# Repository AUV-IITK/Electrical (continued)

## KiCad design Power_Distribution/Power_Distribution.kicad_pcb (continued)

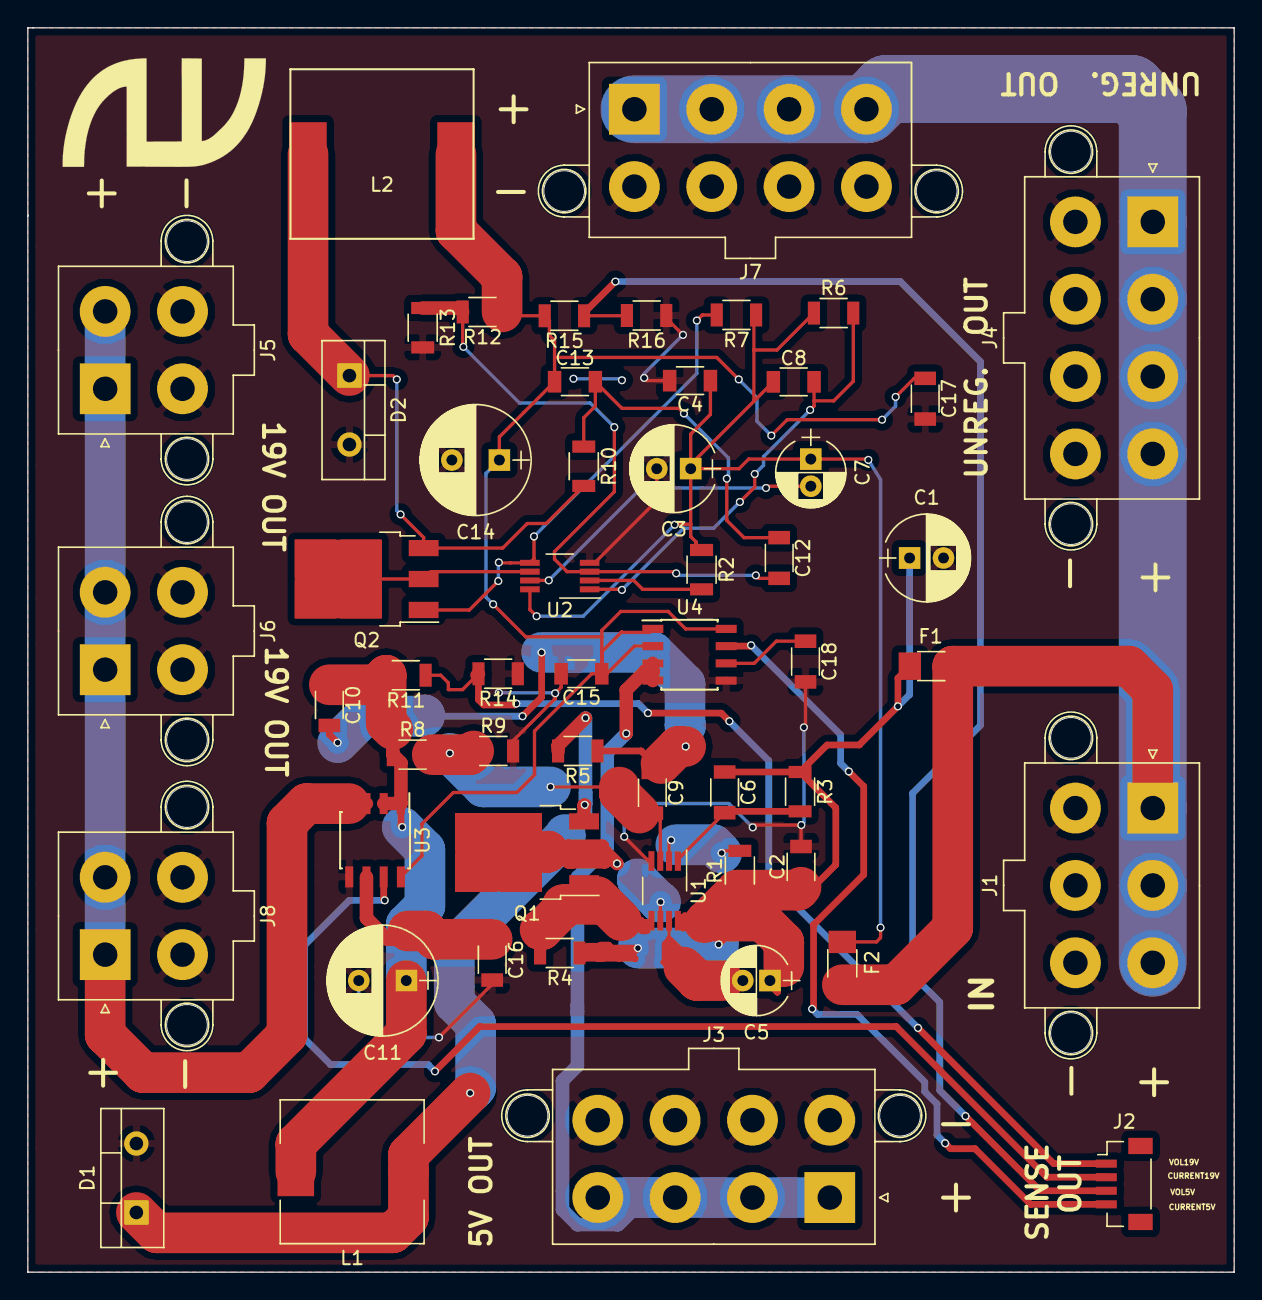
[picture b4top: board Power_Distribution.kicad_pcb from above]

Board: 2 copper layers, 88.9 x 91.7 mm, 54 parts (0 on the bottom side), 30 nets.

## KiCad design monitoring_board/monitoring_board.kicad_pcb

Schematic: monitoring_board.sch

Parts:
D3, D4, D5, D6, D7, D8, D9: LED; LED_D5.0mm
DS1: WC1602A
F1: 30A Polyfuse; Fuse_TE5_Littlefuse-395Series
F2: 4A Polyfuse; Fuse_TE5_Littlefuse-395Series
J1, J2, J3, J4, J7, J8, J9, J10, J11, J12, J13: Conn_01x02; TerminalBlock_bornier-2_P5.08mm
J5: Conn_01x05; Pin_Header_Straight_1x05_Pitch2.54mm
J6: Conn_02x08_Odd_Even; Pin_Header_Straight_2x08_Pitch2.54mm
P1, P17: Digital; Socket_Strip_Arduino_2x18
P2, P14: Power; Socket_Strip_Arduino_1x08
P3, P4, P15, P16: Analog; Socket_Strip_Arduino_1x08
P5, P18: PWM; Socket_Strip_Arduino_1x10
P6, P19: PWM; Socket_Strip_Arduino_1x08
P7, P20: Communication; Socket_Strip_Arduino_1x08
P8, P9, P10, P11, P12, P13, P21, P22, P23, P24, P25, P26: CONN_01X01; Arduino_1pin
Q1, Q2: Q_PMOS_GDS; TO-252-2
R1, R2, R13, R15, R17, R19, R21, R23, R25, R27, R29, R31, R33, R34, R35, R36, R37, R38, R39, R40, R43, R44: 1K; R_Axial_DIN0207_L6.3mm_D2.5mm_P10.16mm_Horizontal
R3, R4, R5, R6, R7, R8, R9, R10, R11: 50m; R_Axial_DIN0207_L6.3mm_D2.5mm_P10.16mm_Horizontal
R12, R14, R16, R18, R20, R22, R24, R26, R28, R30, R32: 24K; R_Axial_DIN0207_L6.3mm_D2.5mm_P10.16mm_Horizontal
R41: R; R_Axial_DIN0207_L6.3mm_D2.5mm_P10.16mm_Horizontal
R42: 220; R_Axial_DIN0207_L6.3mm_D2.5mm_P10.16mm_Horizontal
SW1, SW2: SW_DIP_x01; TerminalBlock_bornier-2_P5.08mm

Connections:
+3V3: J5.2, P2.4, P14.4
+5V: DS1.2, J5.1, P1.35, P1.36, P2.5, P14.5, P17.35, P17.36, R37.2, R42.1
/0(Rx0): P6.8, P19.8
/1(Tx0): P6.7, P19.7
/2(**): J6.1, P6.6, P19.6
/3(**): J6.3, P6.5, P19.5
/4(**): J6.5, P6.4, P19.4
/5(**): J6.7, P6.3, P19.3
/6(**): J6.9, P6.2, P19.2
/7(**): J6.11, P6.1, P19.1
/8(**): J6.13, P5.10, P18.10
/9(**): J6.15, P5.9, P18.9
/10(**): P5.8, P18.8
/11(**): P5.7, P18.7
/12(**): P5.6, P18.6
/13(**): P5.5, P18.5, R36.2
/14(Tx3): P7.1, P20.1
/15(Rx3): P7.2, P20.2
/16(Tx2): P7.3, P20.3
/17(Rx2): P7.4, P20.4
/18(Tx1): P7.5, P20.5
/19(Rx1): P7.6, P20.6
/20(SDA): J5.3, P7.7, P20.7, R38.2
/21(SCL): J5.4, P7.8, P20.8, R39.2
/22: P1.33, P17.33, R40.2
/23: DS1.11, P1.34, P17.34
/24: DS1.12, P1.31, P17.31
/25: DS1.13, P1.32, P17.32
/26: DS1.14, P1.29, P17.29
/27: DS1.6, P1.30, P17.30
/28: DS1.4, P1.27, P17.27
/29: P1.28, P17.28
/30: P1.25, P17.25
/31: P1.26, P17.26
/32: P1.23, P17.23
/33: P1.24, P17.24
/34: P1.21, P17.21
/35: P1.22, P17.22
/36: P1.19, P17.19
/37: P1.20, P17.20
/38: P1.17, P17.17
/39: P1.18, P17.18
/40: P1.15, P17.15
/41: P1.16, P17.16
/42: P1.13, P17.13
/43: P1.14, P17.14
/44: P1.11, P17.11
/45: P1.12, P17.12
/46: P1.9, P17.9
/47: P1.10, P17.10
/48: P1.7, P17.7
/49: P1.8, P17.8
/50(MISO): P1.5, P17.5
/51(MOSI): P1.6, P17.6
/52(SCK): P1.3, P17.3
/53(SS): P1.4, P17.4
/A0: P3.1, P15.1, R16.1, R17.2
/A1: P3.2, P15.2, R12.1, R13.2
/A2: P3.3, P15.3, R20.1, R21.2
/A3: P3.4, P15.4, R24.1, R25.2
/A4: P3.5, P15.5, R32.1, R33.2
/A5: P3.6, P15.6, R14.1, R15.2
/A6: P3.7, P15.7, R18.1, R19.2
/A7: P3.8, P15.8, R26.1, R27.2
/A8: P4.1, P16.1, R30.1, R31.2
/A9: P4.2, P16.2, R22.1, R23.2
/A10: P4.3, P16.3, R28.1, R29.2
/A11: P4.4, P16.4
/A12: P4.5, P16.5
/A13: P4.6, P16.6
/A14: P4.7, P16.7
/A15: P4.8, P16.8
/AREF: P5.3, P18.3
/IOREF: P2.2, P14.2
/Reset: P2.3, P14.3
/SCL: P5.1, P18.1
/SDA: P5.2, P18.2
/VBATT1: Q1.2, SW1.2
/VBATT2: Q2.2, SW2.2
/VESC1: J3.1, R4.1, R12.2
/VESC2: J7.1, R5.1, R20.2
/VESC3: J8.1, R6.1, R24.2
/VESC4: J9.1, R7.1, R32.2
/VESC5: J10.1, R8.1, R14.2
/VESC6: J11.1, R9.1, R18.2
/VESC7: J12.1, R10.1, R26.2
/VESC8: J13.1, R11.1, R30.2
/VIN1: F1.1, R4.2, R5.2, R6.2, R7.2, R8.2, R9.2, R10.2, R11.2, R16.2, R34.2
/VIN2: F2.1, R3.2, R22.2, R35.2
/VNUC: J4.1, R3.1, R28.2
/Vin: P2.8, P14.8
GND: D3.1, D4.1, D5.1, D6.1, D7.1, D8.1, D9.1, DS1.1, DS1.5, DS1.16, J1.2, J2.2, J3.2, J4.2, J5.5, J6.2, J6.4, J6.6, J6.8, J6.10, J6.12, J6.14, J6.16, J7.2, J8.2, J9.2, J10.2, J11.2, J12.2, J13.2, P1.1, P1.2, P2.6, P2.7, P5.4, P14.6, P14.7, P17.1, P17.2, P18.4, R1.1, R2.1, R13.1, R15.1, R17.1, R19.1, R21.1, R23.1, R25.1, R27.1, R29.1, R31.1, R33.1, R41.1
unnamed: D3.2, R34.1
unnamed: D4.2, R35.1
unnamed: D5.2, R36.1
unnamed: D6.2, R37.1
unnamed: D7.2, R38.1
unnamed: D8.2, R39.1
unnamed: D9.2, R40.1
unnamed: DS1.3, R41.2
unnamed: DS1.15, R42.2
unnamed: F1.2, Q1.3, R43.2
unnamed: F2.2, Q2.3, R44.2
unnamed: J1.1, SW1.1
unnamed: J2.1, SW2.1
unnamed: Q1.1, R1.2, R43.1
unnamed: Q2.1, R2.2, R44.1

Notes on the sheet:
Shield for Arduino Mega Rev 3
Holes
Pin duplicates for future use/debugging

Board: 2 copper layers, 97 parts (0 on the bottom side), 107 nets, no tracks yet.

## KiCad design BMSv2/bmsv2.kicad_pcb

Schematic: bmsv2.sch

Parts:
C1, C7: 10n; C_1206
C2, C8, C25, C26, C27, C28, C41, C42, C43, C44, C45, C48, C51: 0.1u; C_1206
C3: 3300p; C_1206
C4, C6, C10, C12: 50u; C_1206
C5: 33p; C_1206
C9: 735p; C_1206
C11: 7.35p; C_1206
C13, C15, C16, C39: 10u; C_1206
C14, C17, C18, C19, C20, C21, C22, C23, C24, C30, C31, C32, C33, C34, C35, C36, C37, C38: 1u; C_1206
C46, C47, C49, C50, C52, C53: 1n; C_1206
CS1, CS2, CS3: ACS725LLC; SOIC-8_3.9x4.9mm_Pitch1.27mm
D1, D3, D4, D5, D6: LED; D_1206
D2: 3.6V; D_1206
D7: 19V; D_1206
D8, D10: D; D_1206
D9, D11: D_Zener; D_1206
F1, F2: Fuse; Fuse_SMD1206_Reflow
J1: B1; Molex_MegaFit_2x01x5.70mm_Angled
J2: B0; Molex_MegaFit_2x01x5.70mm_Angled
J3: BC1; Wafer_Horizontal20x5.8x7RM2.5-7
J4: BC0; Wafer_Horizontal20x5.8x7RM2.5-7
J5: UnRegA; Molex_MegaFit_2x01x5.70mm_Angled
J6: UnRegB; Molex_MegaFit_2x01x5.70mm_Angled
J7: 15V0A; Molex_MegaFit_2x01x5.70mm_Angled
J8: 15V0B; Molex_MegaFit_2x01x5.70mm_Angled
J9: 3V3A; Molex_MegaFit_2x01x5.70mm_Angled
J10: 3V3B; Molex_MegaFit_2x01x5.70mm_Angled
J11: TFT_Header; Berg_11x01
J12: USB_B
J13: Atxmega_Header; Berg_10x02
L1, L2: 20u; L_1206
Q1, Q2, Q5, Q8: Q_PMOS_GSD; SOT-23
Q3, Q4, Q6, Q7: Q_NMOS_GSD; SOT-23
R1, R11: 330K; R_1206
R2, R12: 21K; R_1206
R3, R5, R13, R34, R35, R36, R37, R38, R39, R40, R41, R55, R56, R57, R58, R59, R60, R61, R62: 1K; R_1206
R4: 150; R_1206
R6: 250K; R_1206
R7, R17: 80K; R_1206
R8: 25K; R_1206
R9, R19, R22, R27, R28, R42, R51, R52, R72, R73, R78: 10K; R_1206
R10: 500; R_1206
R14, R15: 2K; R_1206
R16: 1420K; R_1206
R18: 112K; R_1206
R20, R21, R45, R49, R50, R76: 100K; R_1206
R23, R25, R26, R31, R32, R43, R44, R53, R63, R64, R67, R68, R74, R75: 100R; R_1206
R24, R71: 350K; R_1206
R29, R30, R33, R47, R48, R54, R65, R66, R69, R70: 1M; R_1206
R46, R77: R; R_1206
U1, U2: TPS54531; SOIC-8-1EP_3.9x4.9mm_Pitch1.27mm
U3: ATXMEGA128A1U-AU; TQFP-100_14x14mm_Pitch0.5mm
U4, U6: BQ76930; SSOP-20_4.4x6.5mm_Pitch0.65mm
U5, U7: BQ78350-R1; TSSOP-30_4.4x7.8mm_Pitch0.5mm

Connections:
+BATT: CS1.1, CS1.2, F1.1, F2.1, R1.1, R11.1, R23.2, R24.2, R53.2, R71.2, U1.2, U2.2, U4.9, U6.9
/3.3V_CS: CS3.3, CS3.4, J9.1, J10.1
/15V_CS: CS2.3, CS2.4, J7.1, J8.1
/A0: J13.4, U3.6
/A1: J13.6, U3.9
/A2: J13.8, U3.10
/ALERT0: U4.30, U5.2
/ALERT1: U6.30, U7.2
/AREF: J13.2, U3.5
/B0P0: J2.1, Q1.3
/B1P0: J1.1, Q2.3
/BAT0: R24.1, R42.2, U5.7
/BAT1: R71.1, R78.2, U7.7
/BATT_CS: CS1.3, CS1.4, J5.1, J6.1
/C01: J4.6, R35.1
/C02: J4.5, R36.1
/C03: J4.4, R37.1
/C04: J4.3, R38.1
/C05: J4.2, R39.1, R40.1
/C06: J4.1, R41.1
/C11: J3.6, R56.1
/C12: J3.5, R57.1
/C13: J3.4, R58.1
/C14: J3.3, R59.1
/C15: J3.2, R60.1, R61.1
/C16: J3.1, R62.1
/CHG0: Q5.2, U4.2
/CHG1: Q8.2, U6.2
/CSO0: C46.1, CS1.7
/CSO1: C49.1, CS2.7
/CSO2: C52.1, CS3.7
/D0: J13.10, U3.27
/D1: J13.12, U3.28
/D2: J13.14, U3.29
/D3: J13.16, U3.30
/D4: J13.18, U3.17
/D5: J13.20, U3.18
/DAC0: J13.17, U3.97
/DAC1: J13.19, U3.98
/DSG0: Q3.1, R33.1, U4.1
/DSG1: Q6.1, R54.1, U6.1
/MISO: J13.5, U3.21
/MOSI: J13.3, U3.20
/REGOUT0: R20.2, R21.2, R27.1, R28.1, R45.1, U4.8, U5.26
/REGOUT1: R49.2, R50.2, R72.1, R73.1, R76.1, U6.8, U7.26
/RSNS0: Q3.2, R33.2, R43.1, R46.2
/RSNS1: Q6.2, R54.2, R74.1, R77.2
/RX: J13.9, U3.37
/SCK: J13.7, U3.22
/SCL: J13.15, U3.36
/SCL0: R27.2, U4.5, U5.4
/SCL1: R72.2, U6.5, U7.4
/SDA: J13.13, U3.35
/SDA0: R28.2, U4.4, U5.3
/SDA1: R73.2, U6.4, U7.3
/SMBC0: R26.2, U5.13
/SMBC1: R64.2, U7.13
/SMBD0: R25.2, U5.11
/SMBD1: R63.2, U7.11
/SS: J13.1, U3.19
/TFT_CS: J11.7, U3.50
/TFT_DC: J11.9, U3.52
/TFT_MOSI: J11.6, U3.40
/TFT_RESET: J11.8, U3.51
/TFT_SCK: J11.4, U3.42
/TX: J13.11, U3.38
/USBD+: J12.3, U3.32
/USBD-: J12.2, U3.31
/USB_VCC: R3.1, R5.2, U3.99
/VC00: C17.2, R34.2, U4.27
/VC01: C18.2, C19.1, R35.2, U4.26
/VC02: C19.2, C20.1, R36.2, U4.25
/VC03: C20.2, C21.1, R37.2, U4.24
/VC04: C21.2, C22.1, R38.2, U4.23
/VC05: C22.2, C23.1, C24.1, R39.2, U4.22
/VC05B: C23.2, R40.2, U4.21
/VC06: C24.2, R41.2, U4.20
/VC10: C31.2, R55.2, U6.27
/VC11: C32.2, C33.1, R56.2, U6.26
/VC12: C33.2, C34.1, R57.2, U6.25
/VC13: C34.2, C35.1, R58.2, U6.24
/VC14: C35.2, C36.1, R59.2, U6.23
/VC15: C36.2, C37.1, C38.1, R60.2, U6.22
/VC15B: C37.2, R61.2, U6.21
/VC16: C38.2, R62.2, U6.20
/uSCL0: R32.1, U3.16
/uSCL1: R68.1, U3.26
/uSDA0: R31.1, U3.15
/uSDA1: R67.1, U3.25
GND: C1.2, C4.2, C5.1, C6.2, C7.2, C10.2, C11.1, C12.2, C13.1, C14.2, C15.1, C16.2, C17.1, C18.1, C26.1, C27.1, C28.1, C30.2, C31.1, C32.1, C39.2, C42.1, C43.1, C44.1, C45.2, C46.2, C47.2, C48.2, C49.2, C50.2, C51.2, C52.2, C53.2, CS1.5, CS2.5, CS3.5, D1.1, D2.2, D3.1, D4.1, D5.1, D6.1, D7.2, D9.2, D11.2, J1.2, J2.2, J3.7, J4.7, J5.2, J6.2, J7.2, J8.2, J9.2, J10.2, J11.3, J12.4, J12.5, Q1.1, Q2.1, Q4.2, Q5.1, Q7.2, Q8.1, R2.2, R5.1, R7.2, R8.1, R12.2, R17.2, R18.1, R19.2, R29.2, R30.2, R34.1, R42.1, R44.1, R46.1, R47.2, R51.2, R55.1, R65.2, R66.2, R69.2, R75.1, R77.1, R78.1, U1.7, U2.7, U3.3, U3.13, U3.23, U3.33, U3.43, U3.53, U3.63, U3.73, U3.84, U3.93, U4.3, U5.8, U5.9, U5.22, U5.23, U5.25, U5.30, U6.3, U7.8, U7.9, U7.22, U7.23, U7.25, U7.30
unnamed: C1.1, U1.4
unnamed: C2.1, D2.1, L1.1, U1.8
unnamed: C2.2, U1.1
unnamed: C3.1, R8.2
unnamed: C3.2, C5.2, U1.6
unnamed: C7.1, U2.4
unnamed: C8.1, D7.1, L2.1, U2.8
unnamed: C8.2, U2.1
unnamed: C9.1, R18.2
unnamed: C9.2, C11.2, U2.6
unnamed: C14.1, U4.7
unnamed: C16.1, R23.1, U4.15
unnamed: C25.1, C27.2, R43.2, U4.29
unnamed: C25.2, C28.2, R44.2, U4.28
unnamed: C26.2, U5.27
unnamed: C30.1, U6.7
unnamed: C39.1, R53.1, U6.15
unnamed: C41.1, C43.2, R74.2, U6.29
unnamed: C41.2, C44.2, R75.2, U6.28
unnamed: C42.2, U7.27
unnamed: C45.1, CS1.8
unnamed: C47.1, CS1.6
unnamed: C48.1, CS2.8
unnamed: C50.1, CS2.6
unnamed: C51.1, CS3.8
unnamed: C53.1, CS3.6
unnamed: D1.2, R4.2
unnamed: D3.2, R10.2
unnamed: D4.2, R13.2
unnamed: D5.2, R14.1
unnamed: D6.2, R15.1
unnamed: D8.1, D9.1, Q4.1, R47.1, R48.2
unnamed: D8.2, Q5.3, R48.1
unnamed: D10.1, D11.1, Q7.1, R69.1, R70.2
unnamed: D10.2, Q8.3, R70.1
unnamed: F1.2, Q1.2, R14.2
unnamed: F2.2, Q2.2, R15.2
unnamed: J12.1, R3.2
unnamed: Q3.3, Q4.3
unnamed: Q6.3, Q7.3
unnamed: R1.2, R2.1, U1.3
unnamed: R6.2, R7.1, U1.5
unnamed: R9.1, U3.90
unnamed: R10.1, U3.49
unnamed: R11.2, R12.1, U2.3
unnamed: R16.2, R17.1, U2.5
unnamed: R19.1, U4.6
unnamed: R20.1, U5.12
unnamed: R21.1, U5.14
unnamed: R22.1, U4.10
unnamed: R22.2, U4.13
unnamed: R25.1, R29.1, R31.2
unnamed: R26.1, R30.1, R32.2
unnamed: R45.2, U5.24
unnamed: R49.1, U7.12
unnamed: R50.1, U7.14
unnamed: R51.1, U6.6
unnamed: R52.1, U6.10
unnamed: R52.2, U6.13
unnamed: R63.1, R65.1, R67.2
unnamed: R64.1, R66.1, R68.2
unnamed: R76.2, U7.24
unnamed: U4.11, U4.12, U4.14
unnamed: U6.11, U6.12, U6.14

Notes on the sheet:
Connectors
RP, OC Protection
Atxmega
Buck Converters
BM ICs
BM FETs
BM Cell Side
Copyright. AUV-IITK www.auviitk.com
Current Sensors

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
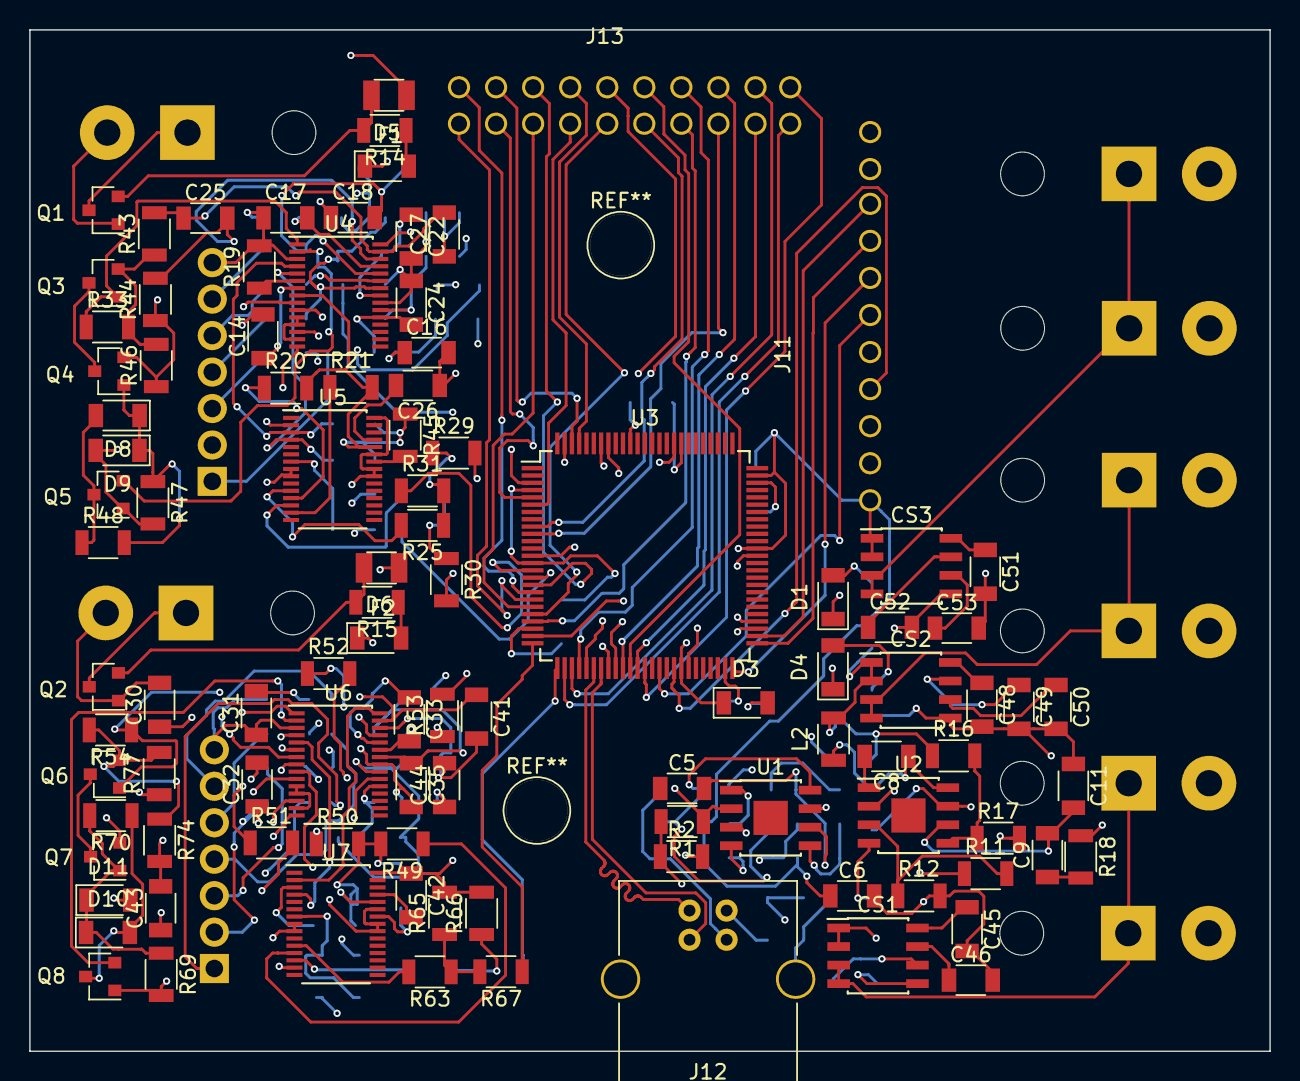
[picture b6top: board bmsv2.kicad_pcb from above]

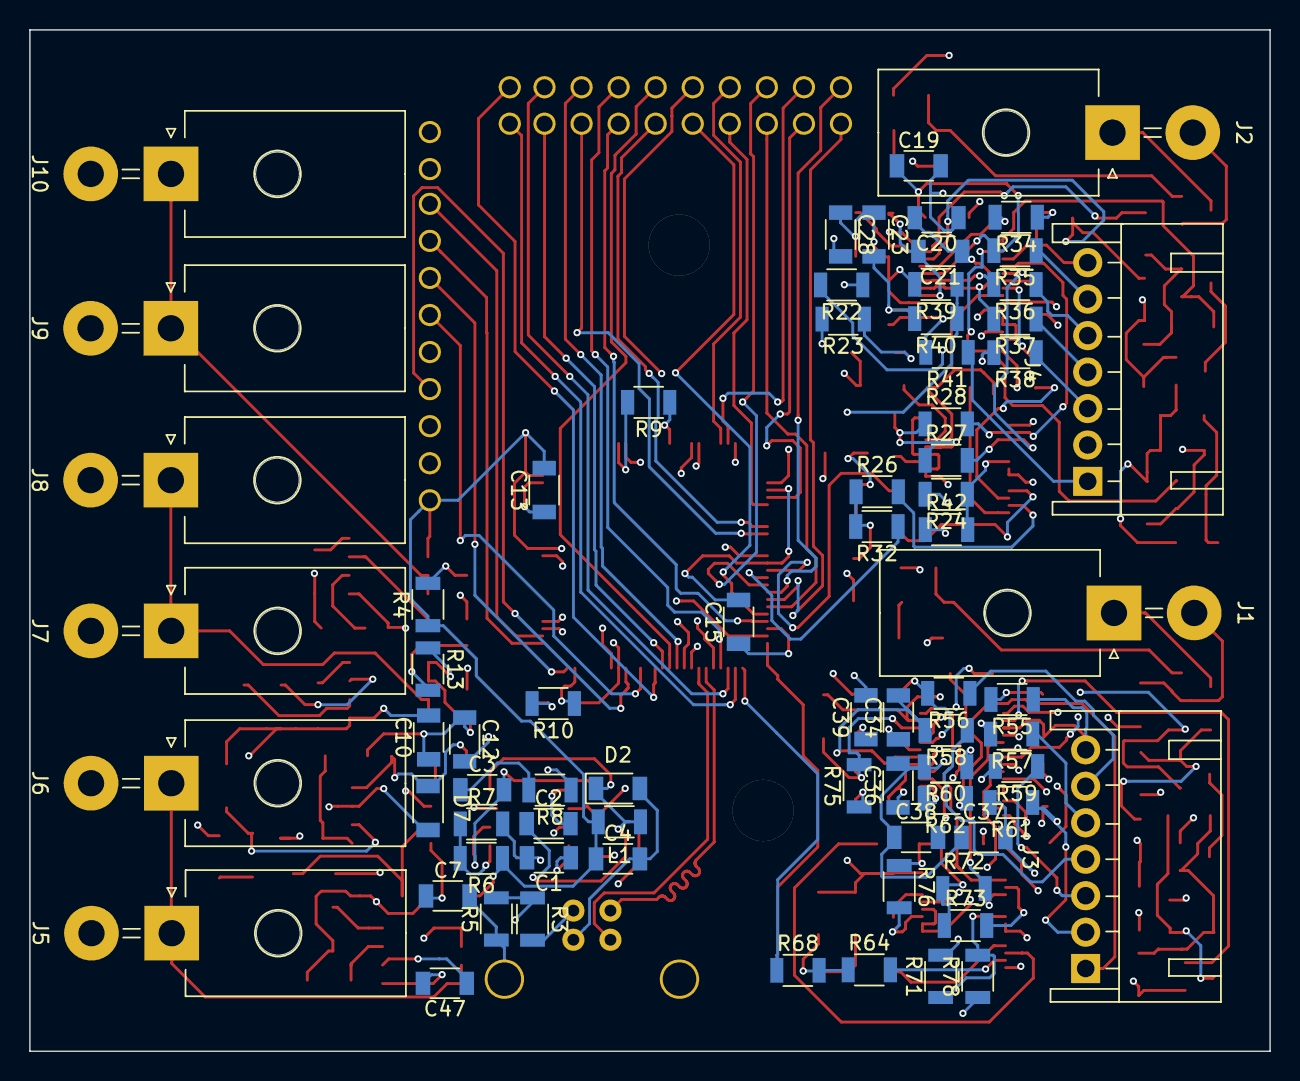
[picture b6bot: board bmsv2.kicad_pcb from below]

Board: 4 copper layers, 85.0 x 70.0 mm, 175 parts (74 on the bottom side), 156 nets.

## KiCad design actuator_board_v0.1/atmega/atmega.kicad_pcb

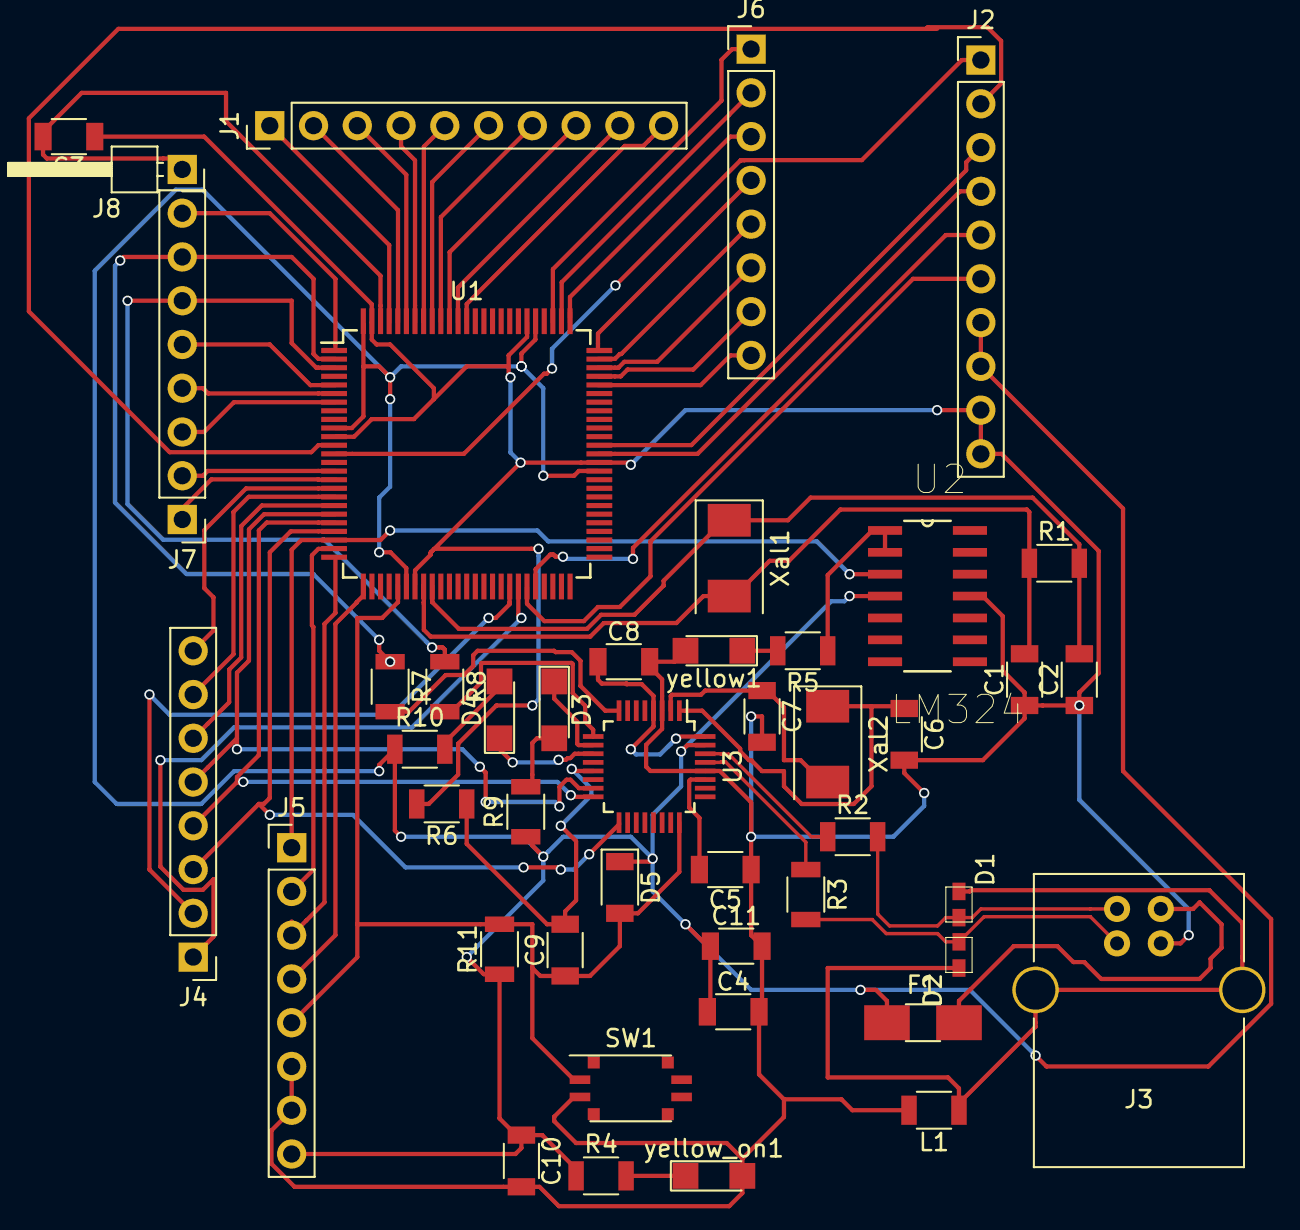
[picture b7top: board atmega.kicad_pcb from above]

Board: 2 copper layers, 45 parts (0 on the bottom side), 70 nets.

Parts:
C1, C2, C6, C7: 22pF; C_1206
C3, C4, C5, C8, C9, C10, C11: 100nF; C_1206
D1, D2: D_TVS; CG0603
D3, D4: LED; LED_1206
D5: D; D_1206
F1: Fuse; Fuse_SMD1206_HandSoldering
J1: Analog pins; Pin_Header_Straight_1x10_Pitch2.54mm
J2: CONN_01X10; Pin_Header_Straight_1x10_Pitch2.54mm
J3: USB_B
J4, J5, J6, J7: CONN_01X08; Pin_Header_Straight_1x08_Pitch2.54mm
J8: CONN_01X01; Pin_Header_Angled_1x01_Pitch2.54mm
L1: Ferrite_Bead; R_1206
R1: 1M; R_1206
R2, R3: 22R; R_1206
R4, R5, R6, R7, R8, R9, R10: 1k; R_1206
R11: 10k; R_1206
SW1: SW_Push; SW_DIP_x2_W5.9mm_Slide_Copal_CVS
U1: ATMEGA2560-8AU; TQFP-100_14x14mm_Pitch0.5mm
U2: LM324; SOIC127P600X175-14N
U3: ATMEGA16U2-AU; LQFP-32_5x5mm_Pitch0.5mm
Xal1, Xal2: 16MHz; Crystal_SMD_0603-2pin_6.0x3.5mm
yellow1: LED; LED_1206
yellow_on1: LED; LED_1206

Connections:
/AREF: C3.2, J8.1, U1.98
/AVCC: C8.1, U3.4, U3.32
/D+: R3.1, U3.29
/D-: R2.1, U3.30
/MISO: J4.3, U1.22, U3.17
/MOSI: J4.4, U1.21, U3.16
/PA0: J6.1, U1.78
/PA1: J6.2, U1.77
/PA2: J6.3, U1.76
/PA3: J6.4, U1.75
/PA4: J6.5, U1.74
/PA5: J6.6, U1.73
/PA6: J6.7, U1.72
/PA7: J6.8, U1.71
/PE3: J7.5, U1.5
/PE4: J7.4, U1.6
/PE5: J7.3, U1.7
/PG5: J7.8, U1.1
/PH3: J7.2, U1.15
/PH4: J7.1, U1.16
/RD+: D2.1, J3.3, R3.2
/RD-: D1.1, J3.2, R2.2
/RESET: C9.1, D5.2, J5.5, R11.2, SW1.1, U1.30, U3.24
/RX0: J7.7, R7.1, U1.2
/RXD1: J2.5, U1.46
/RXD2: J2.2, U1.12
/RXD3: J2.4, U1.63
/SCK: J4.5, U1.20, U3.15
/SCL: J4.2, U1.43
/SDA: J4.1, U1.44
/SHIELD: D1.2, D2.2, J3.5, L1.1
/SS: J4.6, U1.19
/TX0: J7.6, R8.1, U1.3
/TXD1: J2.6, U1.45
/TXD2: J2.1, U1.13
/TXD3: J2.3, U1.64
/UCAP: C5.2, U3.27
/a0: J1.8, U1.90
/a1: J1.7, U1.91
/a2: J1.6, U1.92
/a3: J1.5, U1.93
/a4: J1.4, U1.94
/a5: J1.3, U1.95
/a6: J1.2, U1.96
/a7: J1.1, U1.97
/a8: J1.10, U1.88
/a9: J1.9, U1.89
/p1: J5.1, U1.23, U2.3
/p2: J5.2, U1.24
/p3: J5.3, U1.25
/p4: J5.4, U1.26
/p5: J4.8, U1.17
/p6: J4.7, U1.18
GND: C1.1, C2.1, C3.1, C4.2, C5.1, C6.2, C7.2, C8.2, C10.2, C11.2, J2.9, J2.10, J3.4, J5.6, J5.7, L1.2, R6.2, SW1.2, U1.11, U1.32, U1.62, U1.81, U1.99, U2.11, U3.3, U3.28, yellow1.2, yellow_on1.2
unnamed: C1.2, R1.1, U1.33, Xal1.2
unnamed: C2.2, R1.2, U1.34, Xal1.1
unnamed: C6.1, U3.1, Xal2.1
unnamed: C7.1, U3.2, Xal2.2
unnamed: C9.2, R6.1, U3.13
unnamed: D3.1, U3.10
unnamed: D3.2, R9.2
unnamed: D4.1, U3.11
unnamed: D4.2, R10.2
unnamed: F1.2, J3.1
unnamed: R4.2, yellow_on1.1
unnamed: R5.1, U2.1, U2.2
unnamed: R5.2, yellow1.1
unnamed: R7.2, U3.8
unnamed: R8.2, U3.9
VCC: C4.1, C10.1, C11.1, D5.1, F1.1, J2.7, J2.8, J5.8, R4.1, R9.1, R10.1, R11.1, U1.10, U1.31, U1.61, U1.80, U1.100, U2.4, U3.31

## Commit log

2018-04-04 Move files from personal repo
2018-04-10 Schematic update
2018-04-12 Make corrections to the previous commit
2018-04-15 Add motor drivers to the schematic
2018-05-04 Move files to a separate directory and remove unnecessary ones
2018-05-04 Commit changes made by KiCad
2018-05-04 Add files via upload
    These are the completed design of pcbs
2018-05-04 This is the pcb design without exposing traces
2018-05-07 This is the tentatively final model of the PCB
2018-11-29 Monitoring board template upload
2018-11-30 Monitoring board schematic update
2018-12-01 Remove unwanted file
2018-12-01 Add LCD
2018-12-02 Monitoring board schematic update and start assigning footprints
2018-12-06 Monitoring board complete assigning footprints
2018-12-06 Monitoring board updates
    1. Change 16-pin header for thruster power to 8 2-pin headers
    2. Replace 16-pin header for thruster signal to different 16-pin header
    3. Move components around (this is making the diff so large)
2018-12-09 Monitoring board: start pcb design
2019-02-28 Anahita PCBs
    These are the PCBs currently in use in the vehicle
2019-04-09 Add ltspice simulation files for hydrophones v2 board
2019-04-30 Add gitignore
2019-04-30 Hydrophones ltspice file update
